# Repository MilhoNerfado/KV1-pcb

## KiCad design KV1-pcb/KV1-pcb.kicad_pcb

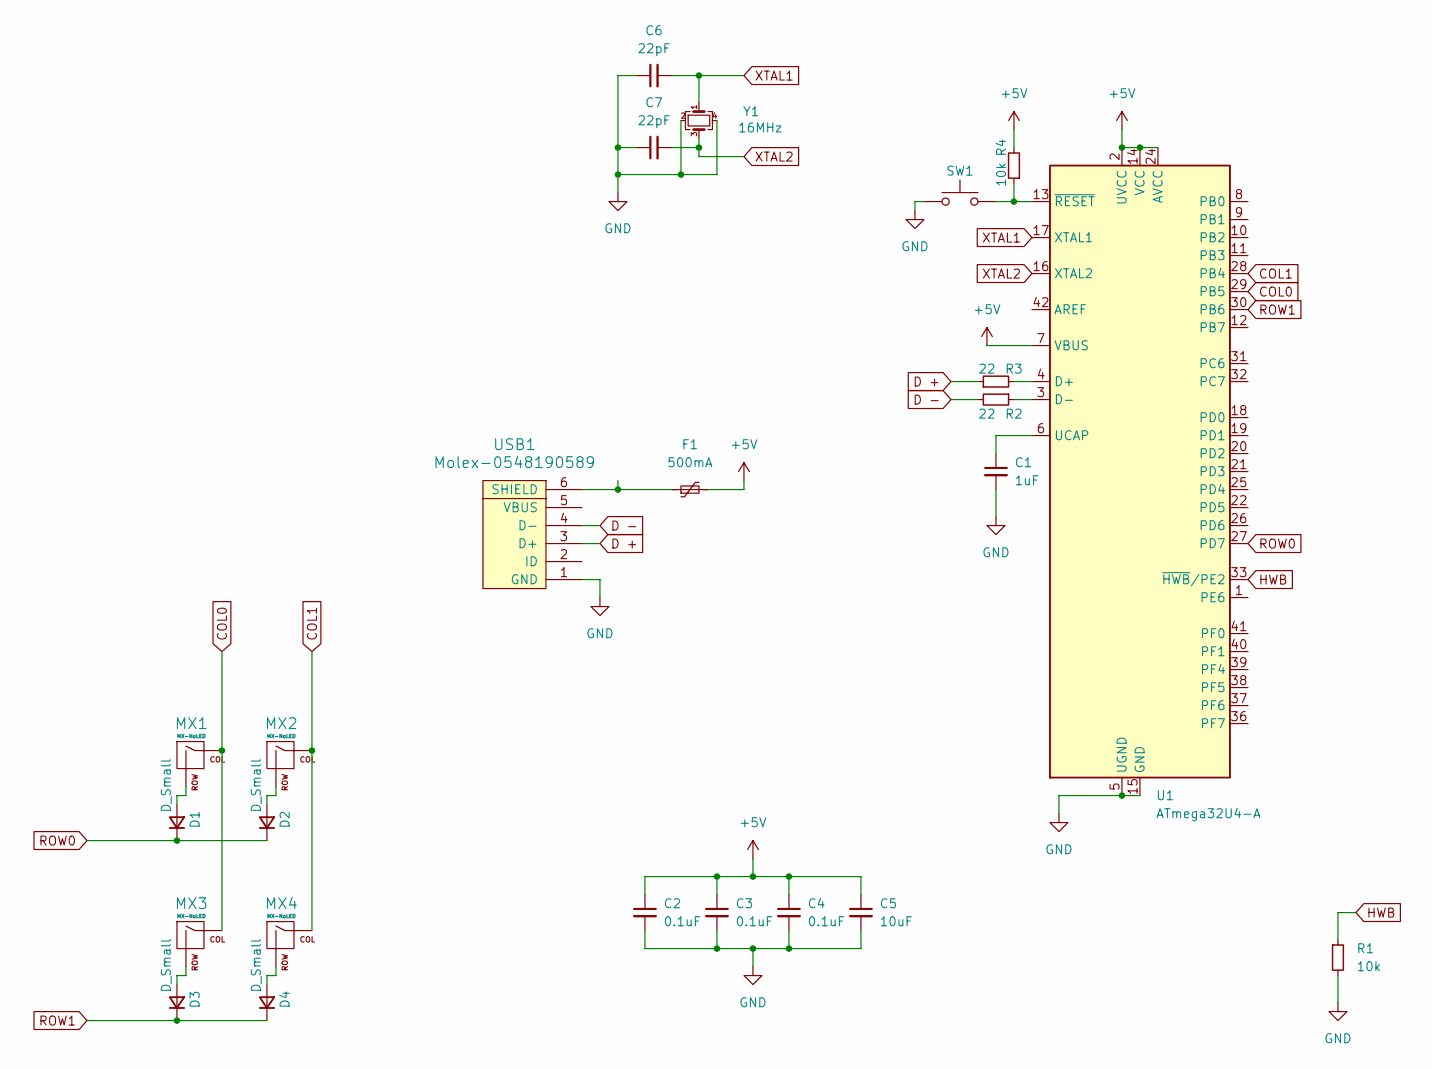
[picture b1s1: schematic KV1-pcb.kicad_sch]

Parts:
C1: 1uF; C_0805_2012Metric
C2, C3, C4: 0.1uF; C_0805_2012Metric
C5: 10uF; C_0805_2012Metric
C6, C7: 22pF; C_0805_2012Metric
D1, D2, D3, D4: D_Small; D_SOD-123
F1: 500mA; Fuse_1206_3216Metric
MX1, MX2, MX3, MX4: MX-NoLED; MX-1U-NoLED
R1, R4: 10k; R_0805_2012Metric
R2, R3: 22; R_0805_2012Metric
SW1: SW_Push; SKQG-1155865
U1: ATmega32U4-A; TQFP-44_10x10mm_P0.8mm
USB1: Molex-0548190589
Y1: 16MHz; Crystal_SMD_3225-4Pin_3.2x2.5mm

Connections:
+5V: C2.1, C3.1, C4.1, C5.1, F1.2, R4.2, U1.2 (UVCC), U1.7 (VBUS), U1.14 (VCC), U1.24 (AVCC), U1.34 (VCC), U1.44 (AVCC)
COL0: MX1.1 (COL), MX3.1 (COL), U1.29 (PB5)
COL1: MX2.1 (COL), MX4.1 (COL), U1.28 (PB4)
D +: R3.1, USB1.3 (D+)
D -: R2.2, USB1.4 (D-)
GND: C1.2, C2.2, C3.2, C4.2, C5.2, C6.1, C7.1, R1.2, SW1.1, U1.5 (UGND), U1.15 (GND), U1.23 (GND), U1.35 (GND), U1.43 (GND), USB1.1 (GND), Y1.2, Y1.4
HWB: R1.1, U1.33 (~HWB/PE2)
unnamed: D1.2 (A), MX1.2 (ROW)
unnamed: D2.2 (A), MX2.2 (ROW)
unnamed: D3.2 (A), MX3.2 (ROW)
unnamed: D4.2 (A), MX4.2 (ROW)
unnamed: R3.2, U1.4 (D+)
unnamed: R2.1, U1.3 (D-)
unnamed: C1.1, U1.6 (UCAP)
unnamed: R4.1, SW1.2, U1.13 (~RESET)
unnamed: F1.1, USB1.6 (SHIELD)
ROW0: D1.1 (K), D2.1 (K), U1.27 (PD7)
ROW1: D3.1 (K), D4.1 (K), U1.30 (PB6)
XTAL1: C6.2, U1.17 (XTAL1), Y1.1
XTAL2: C7.2, U1.16 (XTAL2), Y1.3

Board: 2 copper layers, 24 parts (20 on the bottom side), 20 nets, no tracks yet.

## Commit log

2024-03-08 Add submodules
2024-03-08 Add footprint libs
2024-03-08 Finaliza esquemático e footprint
2024-03-08 Progressing on PCD design
